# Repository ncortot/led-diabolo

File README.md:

diabolo
=======

A tiny board for measurements and LED control on a Diabolo.

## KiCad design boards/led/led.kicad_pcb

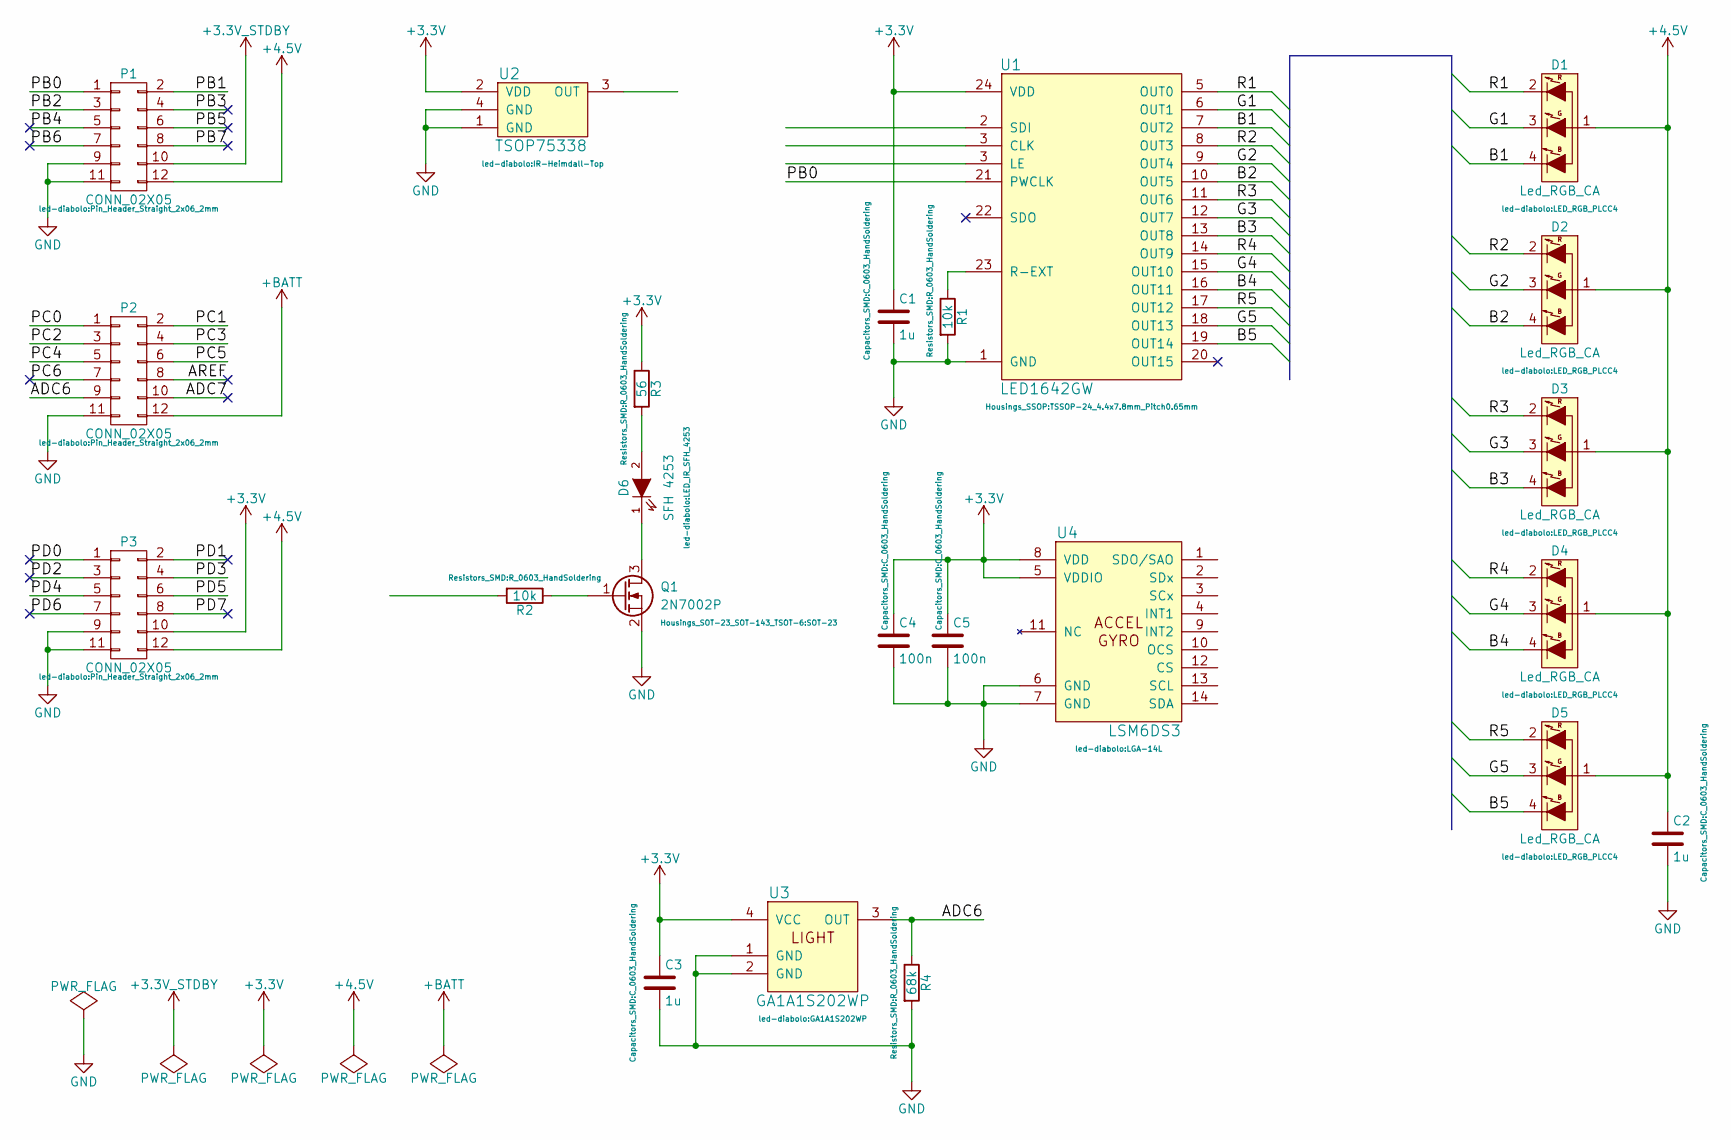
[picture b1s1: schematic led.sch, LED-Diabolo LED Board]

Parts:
C1, C2, C3: 1u; C_0603_HandSoldering
C4, C5: 100n; C_0603_HandSoldering
D1, D2, D3, D4, D5: Led_RGB_CA; LED_RGB_PLCC4
D6: SFH 4253; LED_IR_SFH_4253
P1, P2, P3: CONN_02X05; Pin_Header_Straight_2x06_2mm
Q1: 2N7002P; SOT-23
R1, R2: 10k; R_0603_HandSoldering
R3: 56; R_0603_HandSoldering
R4: 68k; R_0603_HandSoldering
U1: LED1642GW; TSSOP-24_4.4x7.8mm_Pitch0.65mm
U2: TSOP75338; IR-Heimdall-Top
U3: GA1A1S202WP
U4: LSM6DS3; LGA-14L

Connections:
+3.3V_STBY: P1.10
+3V3: C1.1, C3.1, C4.1, C5.1, P3.10, R3.1, U1.24 (VDD), U2.2 (VDD), U3.4 (VCC), U4.5 (VDDIO), U4.8 (VDD)
+4.5V: C2.1, D1.1, D2.1, D3.1, D4.1, D5.1, P1.12, P3.12
+BATT: P2.12
/ADC6: P2.9, R4.1, U3.3 (OUT)
/ADC7: P2.10
/AREF: P2.8
/B1: D1.4 (B), U1.7 (OUT2)
/B2: D2.4 (B), U1.10 (OUT5)
/B3: D3.4 (B), U1.13 (OUT8)
/B4: D4.4 (B), U1.16 (OUT11)
/B5: D5.4 (B), U1.19 (OUT14)
/G1: D1.3 (G), U1.6 (OUT1)
/G2: D2.3 (G), U1.9 (OUT4)
/G3: D3.3 (G), U1.12 (OUT7)
/G4: D4.3 (G), U1.15 (OUT10)
/G5: D5.3 (G), U1.18 (OUT13)
/PB0: P1.1, U1.21 (PWCLK)
/PB1: P1.2
/PB2: P1.3
/PB3: P1.4
/PB4: P1.5
/PB5: P1.6
/PB6: P1.7
/PB7: P1.8
/PC0: P2.1
/PC1: P2.2
/PC2: P2.3
/PC3: P2.4
/PC4: P2.5
/PC5: P2.6
/PC6: P2.7
/PD0: P3.1
/PD1: P3.2
/PD2: P3.3
/PD3: P3.4
/PD4: P3.5
/PD5: P3.6
/PD6: P3.7
/PD7: P3.8
/R1: D1.2 (R), U1.5 (OUT0)
/R2: D2.2 (R), U1.8 (OUT3)
/R3: D3.2 (R), U1.11 (OUT6)
/R4: D4.2 (R), U1.14 (OUT9)
/R5: D5.2 (R), U1.17 (OUT12)
GND: C1.2, C2.2, C3.2, C4.2, C5.2, P1.9, P1.11, P2.11, P3.9, P3.11, Q1.2 (S), R1.2, R4.2, U1.1 (GND), U2.1 (GND), U2.4 (GND), U3.1 (GND), U3.2 (GND), U4.6 (GND), U4.7 (GND)
unnamed: D6.1 (K), Q1.3 (D)
unnamed: D6.2 (A), R3.2
unnamed: Q1.1 (G), R2.1
unnamed: R1.1, U1.23 (R-EXT)

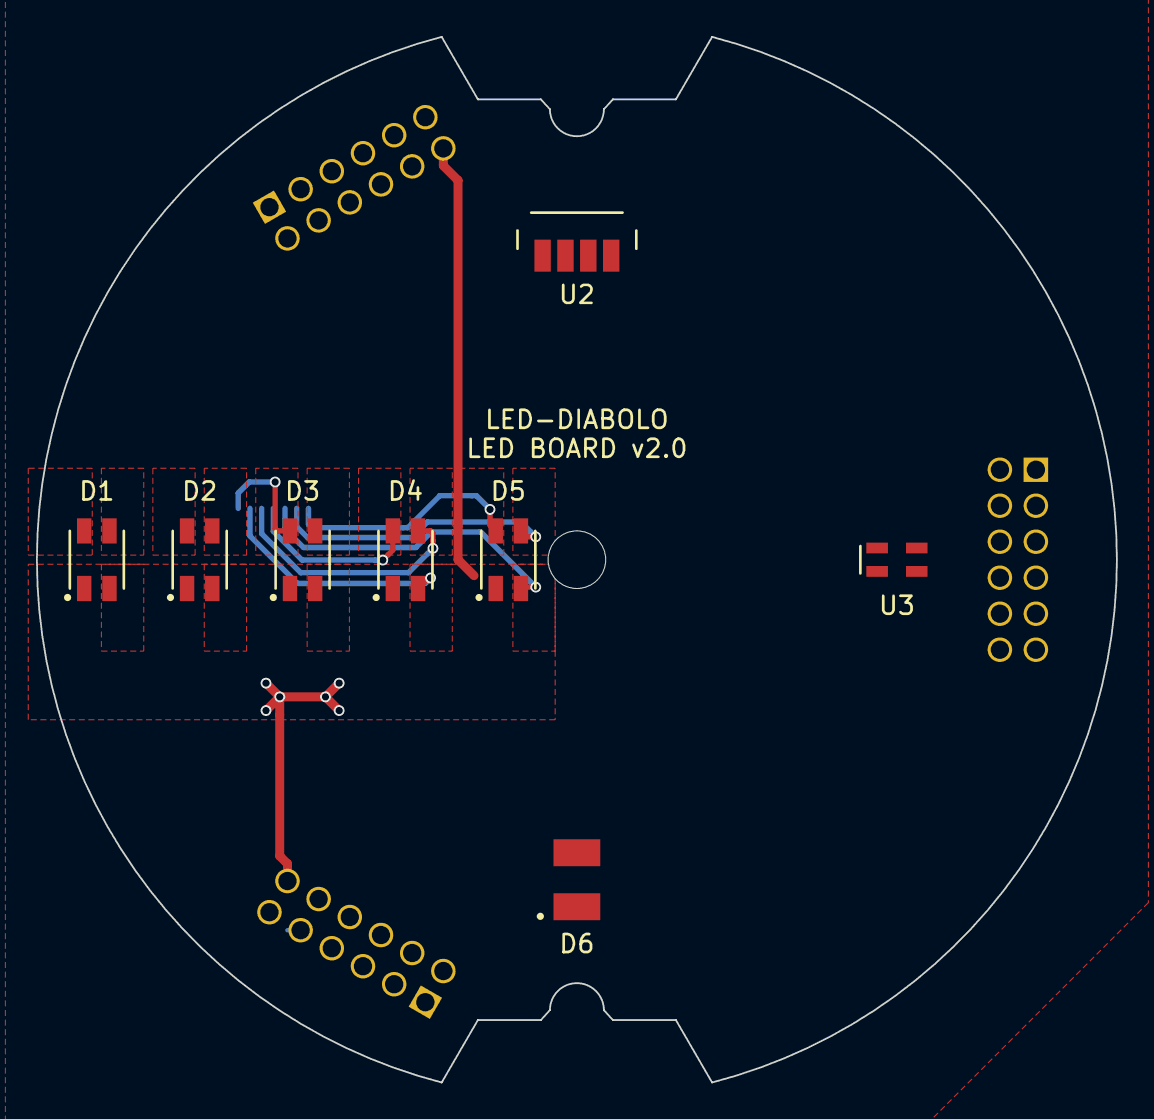
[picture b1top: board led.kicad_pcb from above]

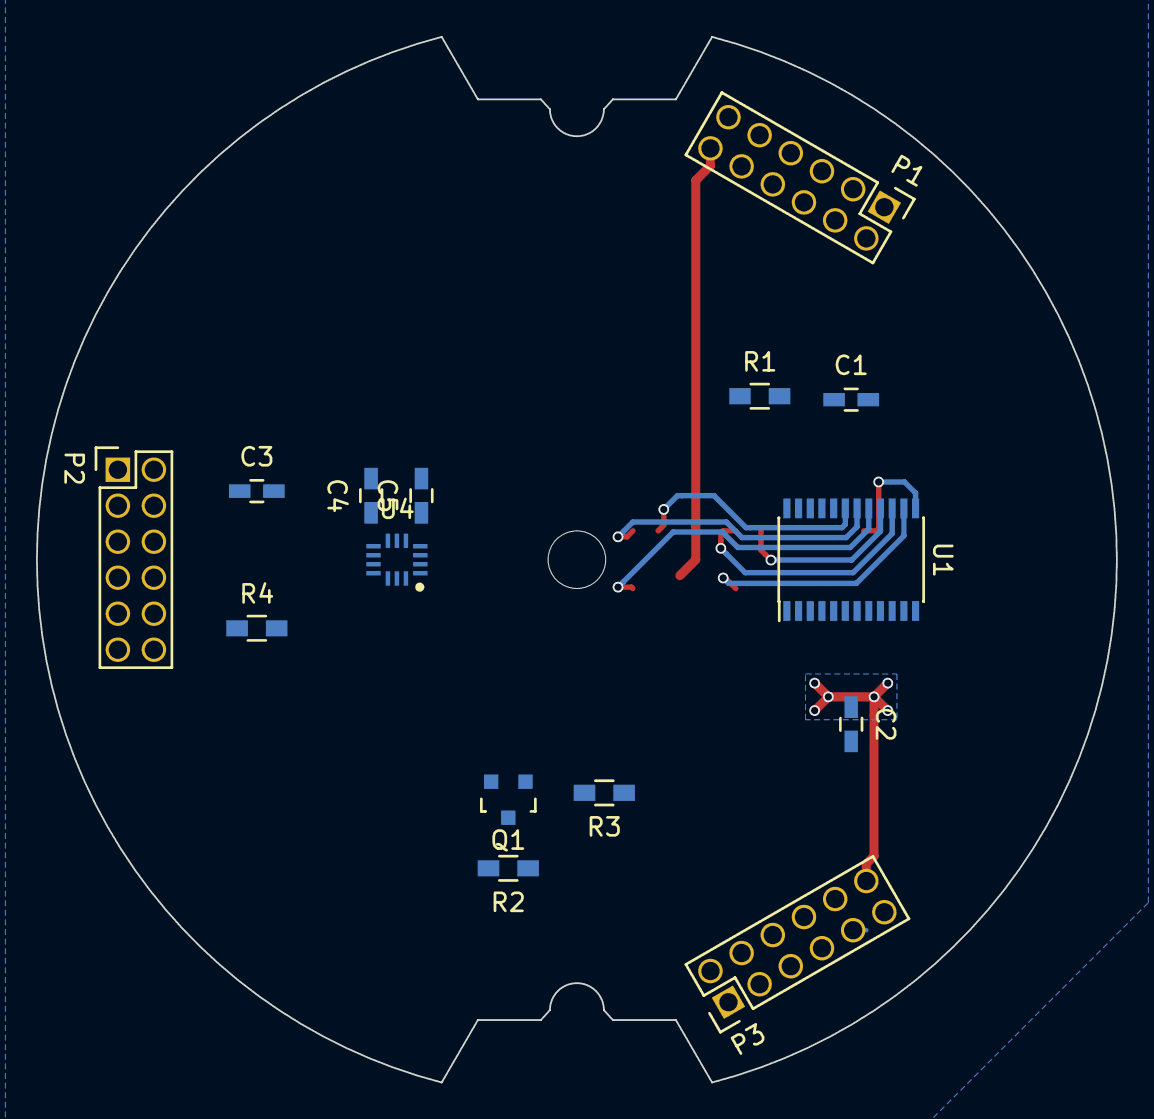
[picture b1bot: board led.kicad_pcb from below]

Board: 2 copper layers, 60.0 x 58.1 mm, 24 parts (15 on the bottom side), 24 nets.

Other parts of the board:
SW1: MountingHole_3-5mm

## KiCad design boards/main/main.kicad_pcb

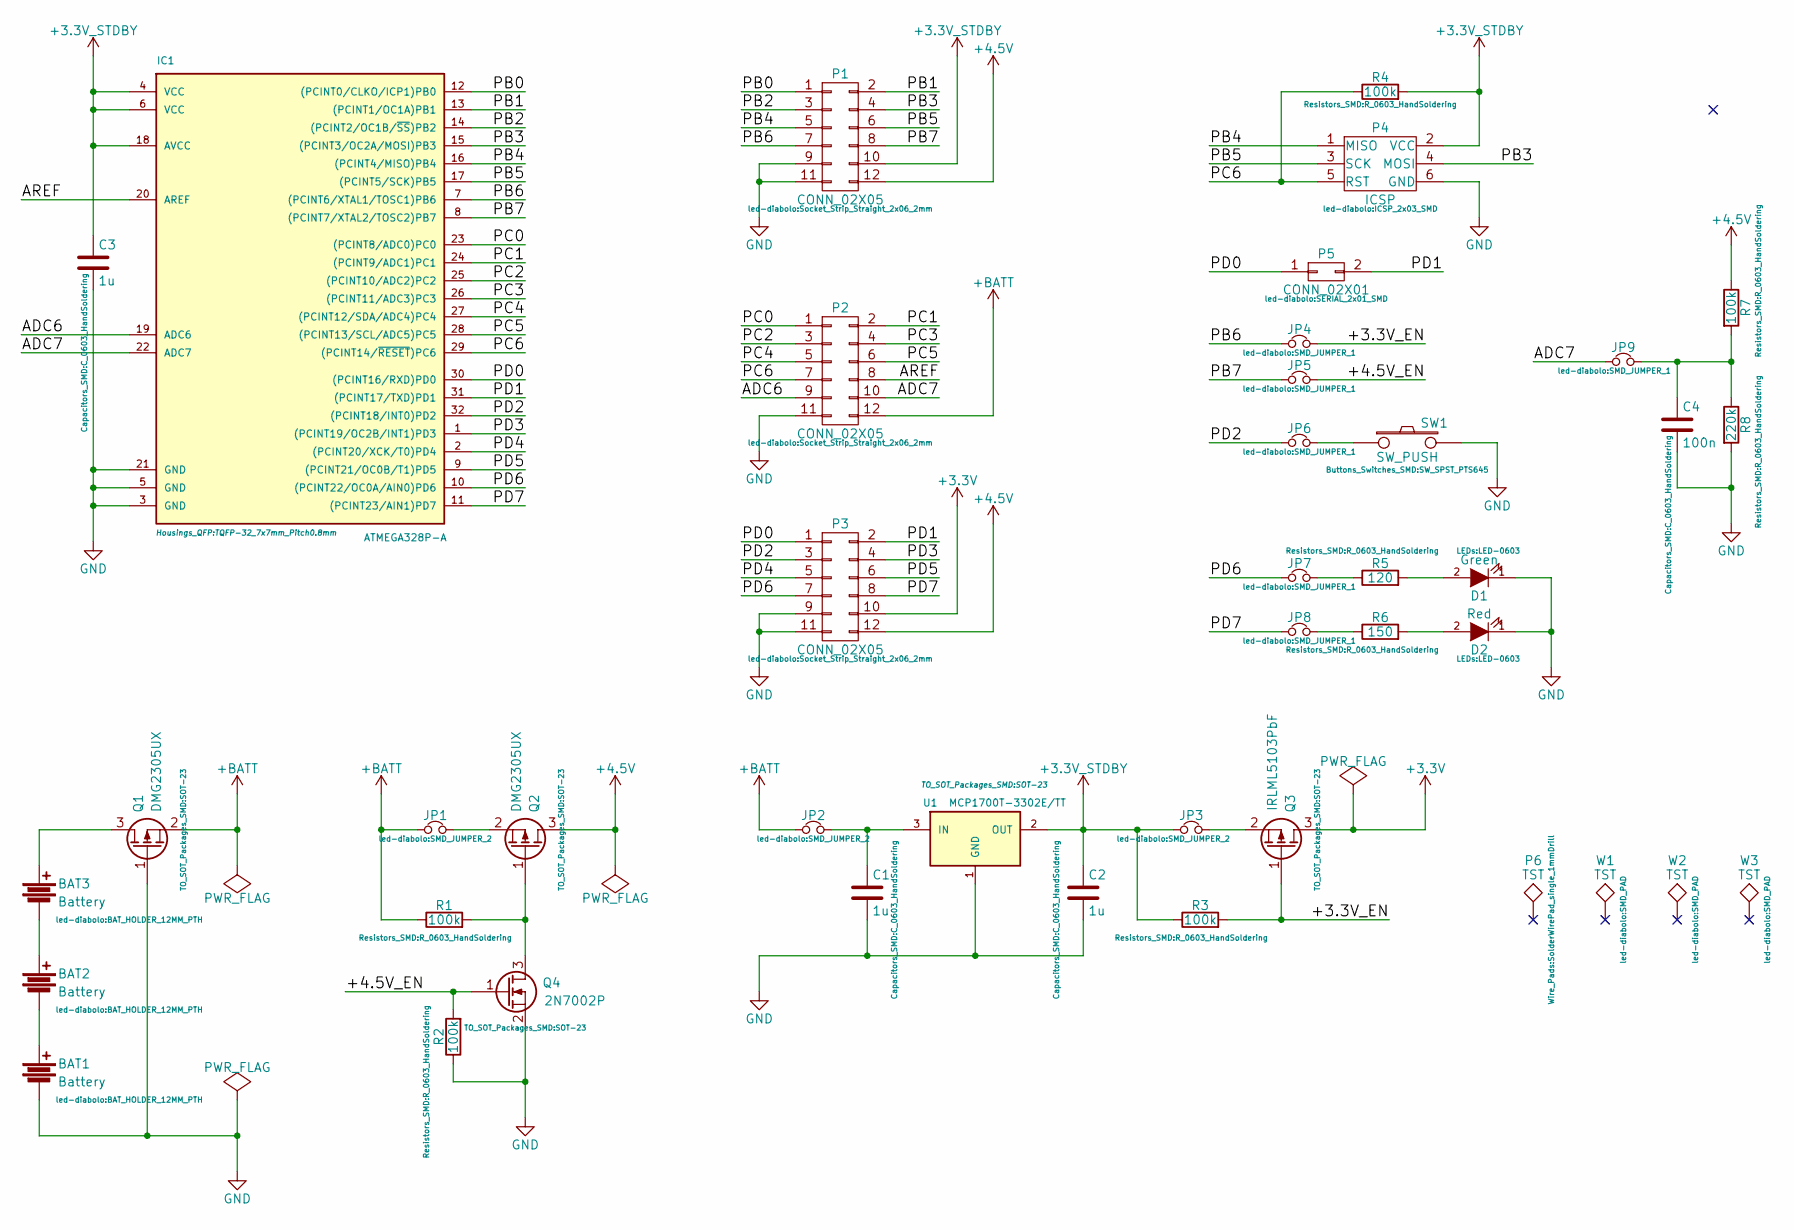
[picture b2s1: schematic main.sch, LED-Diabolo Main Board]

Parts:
BAT1, BAT2, BAT3: Battery; BAT_HOLDER_12MM_PTH
C1, C2, C3: 1u; C_0603_HandSoldering
C4: 100n; C_0603_HandSoldering
D1: Green; LED-0603
D2: Red; LED-0603
IC1: ATMEGA328P-A; TQFP-32_7x7mm_Pitch0.8mm
JP1, JP2, JP3: Jumper_NC_Small; SMD_JUMPER_2
JP4, JP5, JP6, JP7, JP8, JP9: Jumper_NC_Small; SMD_JUMPER_1
P1, P2, P3: CONN_02X05; Socket_Strip_Straight_2x06_2mm
P4: ICSP; ICSP_2x03_SMD
P5: CONN_02X01; SERIAL_2x01_SMD
P6: TST; SolderWirePad_single_1mmDrill
Q1, Q2: DMG2305UX; SOT-23
Q3: IRLML5103PbF; SOT-23
Q4: 2N7002P; SOT-23
R1, R2, R3, R4, R7: 100k; R_0603_HandSoldering
R5: 120; R_0603_HandSoldering
R6: 150; R_0603_HandSoldering
R8: 220k; R_0603_HandSoldering
SW1: SW_PUSH; SW_SPST_PTS645
U1: MCP1700T-3302E/TT; SOT-23
W1, W2, W3: TST; SMD_PAD

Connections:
+3.3V_STBY: C2.1, C3.1, IC1.4 (VCC), IC1.6 (VCC), IC1.18 (AVCC), JP3.1, P1.10, P4.2 (VCC), R3.1, R4.2, U1.2 (OUT)
+3V3: P3.10, Q3.3 (D)
+4.5V: P1.12, P3.12, Q2.3 (D), R7.1
+BATT: JP1.1, JP2.1, P2.12, Q1.2 (S), R1.1
/+3.3V_EN: JP4.2, Q3.1 (G), R3.2
/+4.5V_EN: JP5.2, Q4.1 (G), R2.2
/ADC6: IC1.19 (ADC6), P2.9
/ADC7: IC1.22 (ADC7), JP9.1, P2.10
/AREF: IC1.20 (AREF), P2.8
/PB0: IC1.12 ((PCINT0/CLKO/ICP1)PB0), P1.1
/PB1: IC1.13 ((PCINT1/OC1A)PB1), P1.2
/PB2: IC1.14 ((PCINT2/OC1B/~SS~)PB2), P1.3
/PB3: IC1.15 ((PCINT3/OC2A/MOSI)PB3), P1.4, P4.4 (MOSI)
/PB4: IC1.16 ((PCINT4/MISO)PB4), P1.5, P4.1 (MISO)
/PB5: IC1.17 ((PCINT5/SCK)PB5), P1.6, P4.3 (SCK)
/PB6: IC1.7 ((PCINT6/XTAL1/TOSC1)PB6), JP4.1, P1.7
/PB7: IC1.8 ((PCINT7/XTAL2/TOSC2)PB7), JP5.1, P1.8
/PC0: IC1.23 ((PCINT8/ADC0)PC0), P2.1
/PC1: IC1.24 ((PCINT9/ADC1)PC1), P2.2
/PC2: IC1.25 ((PCINT10/ADC2)PC2), P2.3
/PC3: IC1.26 ((PCINT11/ADC3)PC3), P2.4
/PC4: IC1.27 ((PCINT12/SDA/ADC4)PC4), P2.5
/PC5: IC1.28 ((PCINT13/SCL/ADC5)PC5), P2.6
/PC6: IC1.29 ((PCINT14/~RESET~)PC6), P2.7, P4.5 (RST), R4.1
/PD0: IC1.30 ((PCINT16/RXD)PD0), P3.1, P5.1
/PD1: IC1.31 ((PCINT17/TXD)PD1), P3.2, P5.2
/PD2: IC1.32 ((PCINT18/INT0)PD2), JP6.1, P3.3
/PD3: IC1.1 ((PCINT19/OC2B/INT1)PD3), P3.4
/PD4: IC1.2 ((PCINT20/XCK/T0)PD4), P3.5
/PD5: IC1.9 ((PCINT21/OC0B/T1)PD5), P3.6
/PD6: IC1.10 ((PCINT22/OC0A/AIN0)PD6), JP7.1, P3.7
/PD7: IC1.11 ((PCINT23/AIN1)PD7), JP8.1, P3.8
GND: BAT1.2, C1.2, C2.2, C3.2, C4.2, D1.1 (K), D2.1 (K), IC1.3 (GND), IC1.5 (GND), IC1.21 (GND), P1.9, P1.11, P2.11, P3.9, P3.11, P4.6 (GND), Q1.1 (G), Q4.2 (S), R2.1, R8.2, SW1.2, U1.1 (GND)
unnamed: BAT1.1, BAT2.2
unnamed: BAT2.1, BAT3.2
unnamed: BAT3.1, Q1.3 (D)
unnamed: C1.1, JP2.2, U1.3 (IN)
unnamed: C4.1, JP9.2, R7.2, R8.1
unnamed: D1.2 (A), R5.2
unnamed: D2.2 (A), R6.2
unnamed: JP1.2, Q2.2 (S)
unnamed: JP3.2, Q3.2 (S)
unnamed: JP6.2, SW1.1
unnamed: JP7.2, R5.1
unnamed: JP8.2, R6.1
unnamed: Q2.1 (G), Q4.3 (D), R1.2

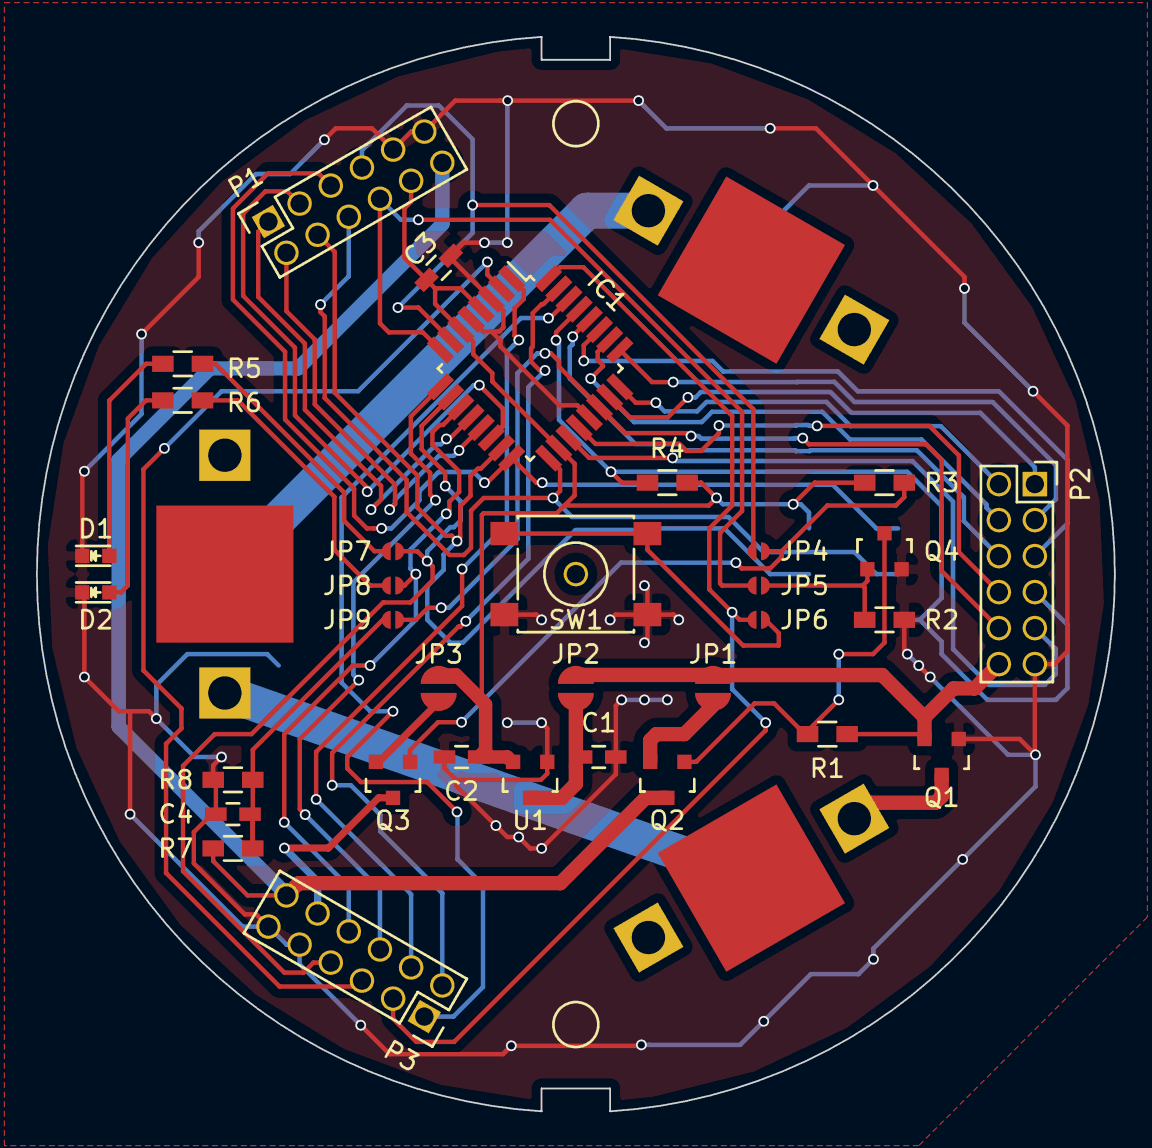
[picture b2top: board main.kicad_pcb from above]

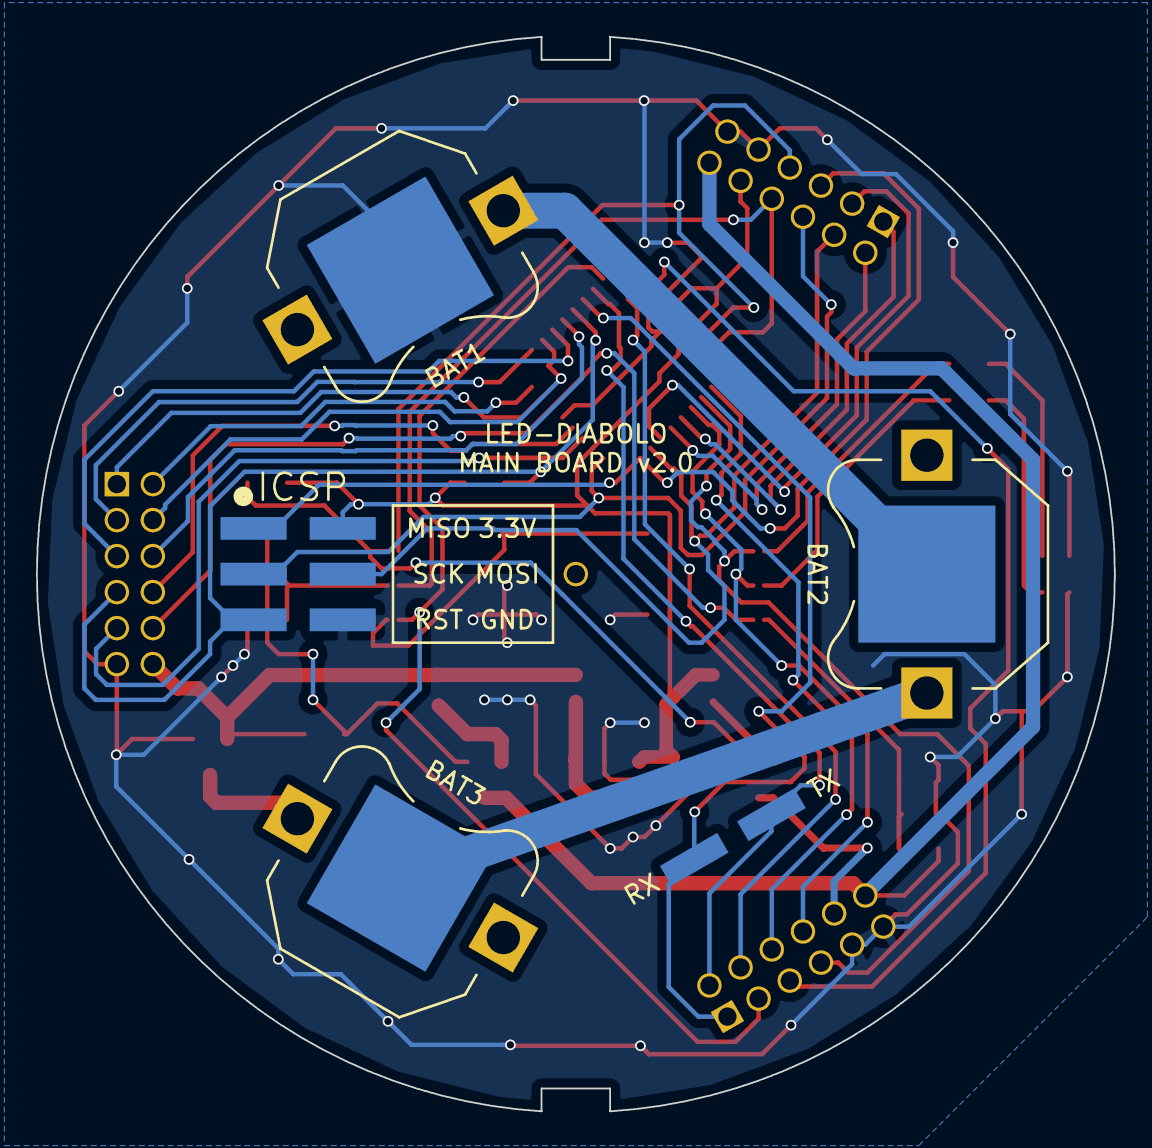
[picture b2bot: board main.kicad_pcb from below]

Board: 2 copper layers, 59.9 x 59.7 mm, 42 parts (5 on the bottom side), 46 nets.

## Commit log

2014-04-15 Eagle schematics
2014-04-15 Adding ATMEGA328P to the library
2014-04-15 Adding ADXL362 breakout
2014-04-15 Add batteries
2014-04-15 Add a pushbutton
2014-04-15 More connexions
2014-04-15 Minor update
2014-04-15 Adding PDFs
2014-04-16 Adding more components
2014-04-21 Bootstrap core board program
2014-04-21 Add programmer board code
2014-04-21 Rename packages
2014-04-22 Buind environment for Arduino
2014-04-22 Add a serial monitor
2014-06-09 LED driver test code
2014-06-09 LED1642GW setup using timer 2
2014-06-10 LED configuration fix
2014-06-10 Simple color demo
2014-06-10 Typo
2014-08-02 Cross-platform Makefile update
2014-08-02 Adding IRLib
2014-08-02 IR testing code
2014-08-03 Better Makefile configuration
2014-08-03 Remove AVR ISP programmer code
    This is not directly a part of the project, you can use any programmer.
    The Teensy 3.x AVR ISP programmer codebase can be found at:
    https://github.com/ncortot/teensy-avr-isp
2014-08-03 Skeleton for the receiver project
2014-08-03 Power the IR receiver directly through the ATMEGA pins
2014-08-03 Simpler serial monitor running
2014-08-03 Move remote commands definition to remote.h
2014-08-03 Serial monitor at 115200bps
2014-08-03 Use the clock output on PB0 for the led driver PWM clock
2014-08-03 IR commands debug
2014-08-16 Schematic update
2014-08-18 Schematics update with more components
2014-08-23 Board layout
2014-08-23 Adding more vias for GND
2014-08-24 Board update
2014-08-24 Adding Gerber files archive
2014-08-24 Parts library cleanup
2014-08-25 Power ON/OFF button handling
2014-08-25 Put the LED driver in auto power shutdown when sleeping
2015-08-10 Repo reorganization
2015-08-10 Code update
2015-08-10 Kicad project for the main board v2
2015-08-10 Move batteries to the bottom of the main board
2015-08-10 Power supply stages update
2015-08-11 Main board update
2015-08-11 Adding stacking connections
2015-08-11 Schematic fixes
2015-08-11 Schematic reorganization
2015-08-12 Add jumper footprints
2015-08-12 Update some libraries
2015-08-12 Use 02x12 2mm pitch headers
2015-08-12 Missing 2mm headers footprint
2015-08-12 Add some components
2015-08-13 Use standard 0603 LEDs
2015-08-13 Small fixes
2015-08-14 Fix some footprints
2015-08-15 Components update
2015-08-16 Remove silkscreen around PTH
2015-08-16 Placing components
2015-08-16 Routing
2015-08-17 More routing
2015-08-23 Main board routing
2015-09-01 Add version information
2015-09-01 Adding fab files
2015-09-01 Export config
2015-09-01 LED board layout
2015-09-01 Adding schematic PDF
2015-09-01 Adding 2mm pin headers
2015-09-01 LED board outline
2015-09-01 Outline fix
2015-09-05 Adding LED1642GW LED driver
2015-09-05 Add 5 RGB LEDs
2015-09-06 LED board update
